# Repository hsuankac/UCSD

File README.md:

# UCSD
Embedded Systems Engineering Certificate

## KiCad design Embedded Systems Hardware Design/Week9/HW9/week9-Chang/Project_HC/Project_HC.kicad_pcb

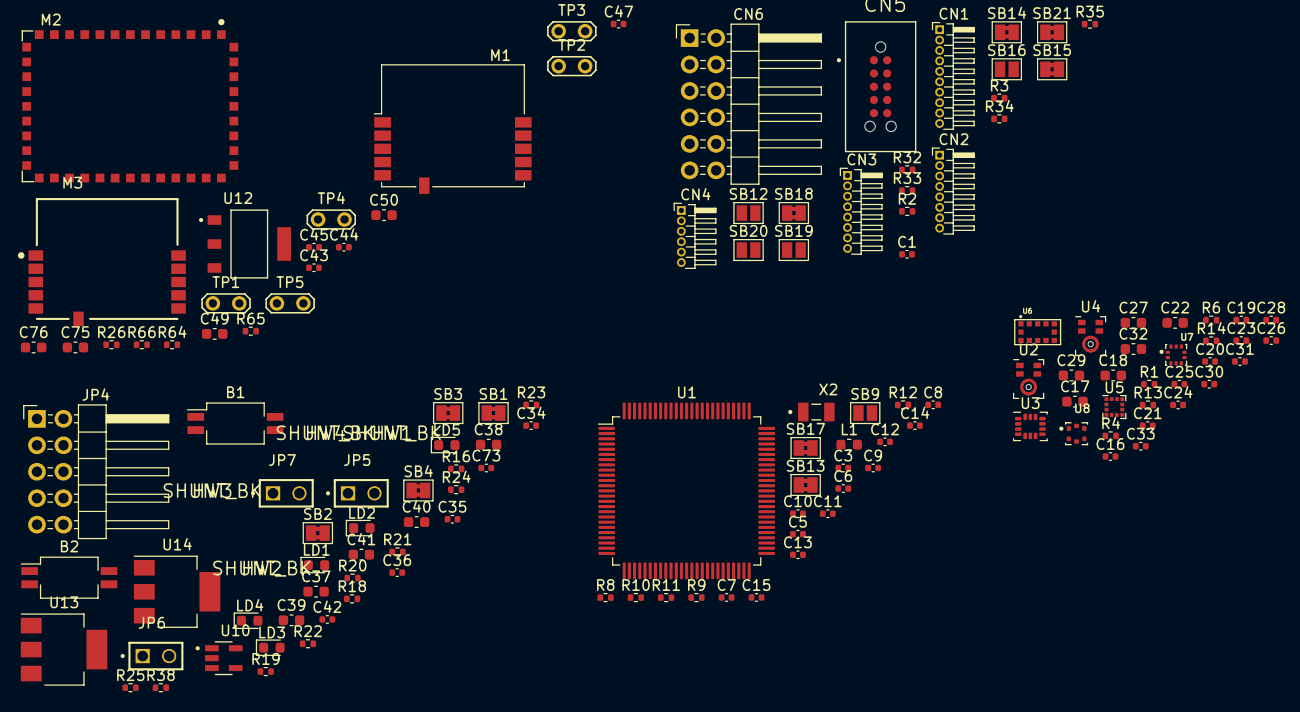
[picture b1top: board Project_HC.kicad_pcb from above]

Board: 2 copper layers, 137 parts (0 on the bottom side), 91 nets, no tracks yet.

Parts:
B1: SW-PUSH-CMS_BLUE; SW_DIP_SPSTx02_Slide_Copal_CHS-02B_W7.62mm_P1.27mm
B2: SW-PUSH-CMS_BLACK; SW_DIP_SPSTx02_Slide_Copal_CHS-02B_W7.62mm_P1.27mm
C1, C3, C5, C6, C7, C9, C10, C11, C12, C13, C16, C19, C20, C21, C23, C25, C26, C28, C30, C31, C33, C34, C36, C42, C43, C44, C45, C73: 100nF; C_0402_1005Metric
C8, C24: 1uF; C_0402_1005Metric
C14, C15: 5.1pF; C_0402_1005Metric
C17, C22: 10uf; C_0603_1608Metric
C18, C27, C32: 4.7uF; C_0603_1608Metric
C29, C75, C76: 2.2uF; C_0603_1608Metric
C35: 10pF; C_0402_1005Metric
C37: 10pF; C_0603_1608Metric
C38, C39, C40, C41, C49, C50: 10uF; C_0603_1608Metric
C47: 2.2uF; C_0402_1005Metric
CN1: Header 10X1_Female_SMD; PinHeader_1x10_P1.00mm_Horizontal
CN2, CN3: Header 8X1_Female_SMD; PinHeader_1x08_P1.00mm_Horizontal
CN4: Header 6X1_Female_SMD; PinHeader_1x06_P1.00mm_Horizontal
CN5: TC2050-IDC-NL; TAG-CONNECT_TC2050-IDC-NL
CN6: HEADER_2X6_PMOD; PinHeader_2x06_P2.54mm_Horizontal
HW1, HW2, HW3, HW4: SHUNT_BK; Samtec-SNT-100-BK-G-MFG
JP4: HEADER_2X5; PinHeader_2x05_P2.54mm_Horizontal
JP5, JP6, JP7: TSW-102-07-G-S; SAMTEC_TSW-102-07-G-S
L1: FCM1608KF-601T03; L_0603_1608Metric
LD1, LD2, LD3: LED GREEN; LED_0603_1608Metric
LD4: LED YELLOW; LED_0603_1608Metric
LD5: LED BLUE; LED_0603_1608Metric
M1: BT Module; ST_SPBTLE
M2: ISM43362-M3G-L44; INVENTEK_ISM43362-M3G-L44-E_C2.5.0.3_SPI
M3: SPSGRF; XCVR_SPSGRF-868
R1, R2, R4, R12: 0R; R_0402_1005Metric
R3: 1k; R_0402_1005Metric
R6, R13: 10k; R_0402_1005Metric
R8, R11: 2K2; R_0402_1005Metric
R9, R10: 2k2; R_0402_1005Metric
R14, R16: 10K; R_0402_1005Metric
R18, R19, R21, R24: 1K; R_0402_1005Metric
R20, R25: 330R; R_0402_1005Metric
R22: 680R; R_0402_1005Metric
R23: 100k; R_0402_1005Metric
R26: 47K; R_0402_1005Metric
R32, R33, R34, R35: 22R; R_0402_1005Metric
R38: 200k; R_0402_1005Metric
R64, R65, R66: Not Fitted (10k); R_0402_1005Metric
SB1, SB2, SB3, SB4, SB13, SB14, SB15, SB17, SB18, SB21: Close; SolderJumper-2_P1.3mm_Bridged2Bar_Pad1.0x1.5mm
SB9, SB12, SB16, SB19, SB20: Open; SolderJumper-2_P1.3mm_Open_Pad1.0x1.5mm
TP1, TP2, TP3, TP4, TP5: TestPoint_Small; TestPoint_2Pads_Pitch2.54mm_Drill0.8mm
U1: STM32L475VGTx; LQFP-100_14x14mm_P0.5mm
U2, U4: Mic; Knowles_LGA-5_3.5x2.65mm
U3: LSM6DSL; LGA-14_3x2.5mm_P0.5mm_LayoutBorder3x4y
U5: LIS3MDL; LGA-12_2x2mm_P0.5mm
U6: VL53L0X; SENSOR_VL53L0X
U7: LPS22HB; LGA10R50P2X3_200X200X80
U8: HTS221; XDCR_HTS221
U10: TSV631AILT; SOT95P280X145-5N
U12: LT1963EST-3.3; SOT230P700X180-4N
U13: LD1117S50TR; SOT-223-3_TabPin2
U14: LD1117S33TR; SOT-223-3_TabPin2
X2: NX3215SA-32.768K; XTAL_NX3215SA-32.768K-STD-MUA-8

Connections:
+3.3V: C16.1, C17.1, C21.1, C22.1, C27.1, C28.1, C29.1, C30.1, C73.1, R6.2, R23.2, U2.1 (Vdd), U4.1 (Vdd), U6.1 (AVDDVCSEL), U6.11 (AVDD), U8.1 (VDD), U8.6 (CS), U10.5 (V+)
+3V3: C18.1, C19.1, C20.1, C24.1, C25.1, C26.1, C31.1, C32.1, C33.1, C42.1, C43.1, C44.1, C45.1, C47.1, C50.1, C75.1, C76.1, CN2.2 (IOREF), CN2.4 (3V3), CN6.6, CN6.12, JP5.01, JP5.02, M1.5 (VIN), M2.2 (VDD), M2.14 (VDD), M2.15 (VBAT), M3.5 (VIN), R8.1, R9.1, R10.1, R11.1, R13.2, R14.2, R26.2, R64.2, R65.2, R66.2, U3.5 (VDDIO), U3.8 (VDD), U3.12 (CS), U5.5 (Vdd), U5.6 (Vdd_IO), U5.9 (SDO/SA1), U5.10 (~CS), U7.1 (VDD_IO), U7.5 (SD0/SA0), U7.6 (~CS), U7.10 (VDD), U12.3 (OUT)
+5V: C1.1, C38.1, C39.1, C40.1, C41.1, C49.1, CN2.5, CN2.8 (VIN), CN5.1, JP4.1, JP4.2, JP4.3, JP4.4, JP4.5, JP4.6, JP4.8, JP4.9, JP4.10, R2.1, R3.2, R25.2, U12.1 (IN), U13.2 (VO), U13.3 (VI), U14.2 (VO), U14.3 (VI)
ARD.A0-ADC: CN4.1, U1.34 (PC5)
ARD.A1-ADC: CN4.2, U1.33 (PC4)
ARD.A2-ADC: CN4.3, U1.18 (PC3)
ARD.A3-ADC: CN4.4, U1.17 (PC2)
ARD.A4-ADC: CN4.5, U1.16 (PC1)
ARD.A5-ADC: CN4.6, U1.15 (PC0)
ARD.D0-UART4_RX: CN3.1, U1.24 (PA1)
ARD.D1-UART4_TX: CN3.2, U1.23 (PA0)
ARD.D2-INT0_EXTI14: CN3.3, U1.61 (PD14)
ARD.D3-PWM/INT1_EXTI0: CN3.4, U1.35 (PB0)
ARD.D4: CN3.5, U1.26 (PA3)
ARD.D5-PWM: CN3.6, U1.90 (PB4)
ARD.D6-PWM: CN3.7, U1.36 (PB1)
ARD.D7: CN3.8, U1.29 (PA4)
ARD.D8: CN1.1, U1.37 (PB2)
ARD.D9-PWM: CN1.2, U1.77 (PA15)
ARD.D10-SPI_SSN/PWM: CN1.3, U1.25 (PA2)
ARD.D11-SPI1_MOSI/PWM: CN1.4, U1.32 (PA7)
ARD.D12-SPI1_MISO: CN1.5, U1.31 (PA6)
ARD.D13-SPI1_SCK/LED1: CN1.6, U1.30 (PA5)
ARD.D14-I2C1_SDA: CN1.9, R8.2, U1.96 (PB9)
ARD.D15-I2C1_SCL: CN1.10, R9.2, U1.95 (PB8)
DFSDM1_CKOUT: R1.1, U1.40 (PE9), U1.41 (PE10)
DFSDM1_DATIN2: R4.1, U1.38 (PE7)
GND: B1.2, B2.2, C1.2, C3.2, C5.2, C6.2, C7.2, C8.2, C9.1, C10.1, C11.1, C12.1, C13.1, C14.2, C15.2, C16.2, C17.2, C18.2, C19.2, C20.2, C21.2, C22.2, C23.2, C24.2, C25.2, C26.2, C27.2, C28.2, C29.2, C30.2, C31.2, C32.2, C33.2, C34.2, C35.2, C36.2, C37.2, C38.2, C39.2, C40.2, C41.2, C42.2, C43.2, C44.2, C45.2, C47.2, C49.2, C50.2, C73.2, C75.2, C76.2, CN1.7, CN2.6, CN2.7 (GND), CN5.3, CN5.5, CN6.5, CN6.11, JP6.01, JP6.02, JP7.01, JP7.02, LD1.1 (K), LD2.1 (K), LD3.1 (K), LD4.1 (K), LD5.1 (K), M1.6 (GND), M2.1 (GND), M2.3 (GND), M2.17 (GND), M2.20 (GND), M2.35 (GND), M3.6 (GND), R38.2, SB13.1 (A), U1.10 (VSS), U1.19 (VSSA), U1.20 (VREF-), U1.27 (VSS), U1.49 (VSS), U1.74 (VSS), U1.99 (VSS), U2.5 (GND), U3.1 (SDO/SA0), U3.6 (GND), U3.7 (GND), U4.2 (LR), U4.5 (GND), U5.2 (Res), U5.3 (GND), U5.12 (Res), U6.2 (AVSSVCSEL), U6.3 (GND), U6.4 (GND), U6.6 (GND), U6.12 (GND), U7.3 (RES), U7.8 (GND), U7.9 (GND), U8.5 (GND), U10.2 (V-), U12.2 (GND), U13.1 (GND), U14.1 (GND)
HTS221_DRDY_EXTI15: U1.62 (PD15), U8.3 (DRDY)
INTERNAL-I2C2_SCL: R10.2, U1.47 (PB10), U3.13 (SCL), U5.1 (SCL/SPC), U6.10 (SCL), U7.2 (SCL/SPC), U8.2 (SCL/SPC)
INTERNAL-I2C2_SDA: U3.4 (INT1), U3.14 (SDA), U5.11 (SDA/SDI/SDO), U6.9 (SDA), U7.4 (SDA/SDI/SDO), U8.4 (SDA/SDI/SDO)
INTERNAL-SPI3_MISO: M1.8 (SPI_MISO), M2.10 (ADC3/SPI_MISO), M3.8 (SPI_MISO), U1.79 (PC11)
INTERNAL-SPI3_MOSI: M1.9 (SPI_MOSI), M2.9 (ADC4/SPI_MOSI), M3.9 (SPI_MOSI), U1.80 (PC12)
INTERNAL-SPI3_SCK: M1.7 (SPI_CLK), M2.11 (ADC2/SPI_SCK), M3.7 (SPI_CLK), U1.78 (PC10)
INTERNAL-UART3_RX: M2.22 (TX), U1.56 (PD9)
INTERNAL-UART3_TX: M2.21 (RX), U1.55 (PD8)
ISM43362-BOOT0: M2.33 (BOOT0/RES4), U1.51 (PB12)
ISM43362-DRDY_EXTI1: M2.13 (ADC0/DATARDY), U1.98 (PE1)
ISM43362-RST: M2.34 (RSTN), U1.39 (PE8)
ISM43362-WAKEUP: M2.16 (WKUP), U1.52 (PB13)
LED2: R20.2, U1.53 (PB14)
LED3(WIFI) & LED4(BLE): R21.2, R22.2, U1.66 (PC9)
LPS22HB_INT_DRDY_EXTI10: U1.57 (PD10), U7.7 (INT_DRDY)
LSM3MDL_DRDY_EXTI8: U1.65 (PC8), U5.8 (DRDY)
NTERNAL-I2C2_SDA: R11.2, U1.48 (PB11)
unnamed: B1.1, C37.1, R23.1, R24.1
unnamed: B2.1, C35.1, R19.1
unnamed: C5.1, C6.1, L1.2, U1.21 (VREF+), U1.22 (VDDA)
unnamed: C14.1, R12.2, X2.1
unnamed: C15.1, U1.9 (PC15), X2.2
unnamed: C23.1, U5.4 (C1)
unnamed: C34.1, R19.2
unnamed: C36.1, R24.2
unnamed: CN1.8, R2.2
unnamed: CN2.1, R3.1
unnamed: CN5.2, R33.1
unnamed: CN5.4, R32.1
unnamed: CN5.6, R35.1
unnamed: CN5.10, R34.1
unnamed: LD1.2 (A), R25.1
unnamed: LD2.2 (A), R18.1
unnamed: LD3.2 (A), R20.1
unnamed: LD4.2 (A), R21.1
unnamed: LD5.2 (A), R22.1
unnamed: M2.4 (TMS), TP1.1
unnamed: M2.5 (TCK), TP2.1
unnamed: M2.6 (TDI), TP3.1
unnamed: M2.7 (TDO), TP4.1
unnamed: M2.8 (TDRSTN), TP5.1
unnamed: M2.28 (CFG0), R66.1
unnamed: M2.29 (CFG1), R64.1, R65.1
unnamed: R1.2, U2.3 (CLK), U4.3 (CLK)
unnamed: R4.2, U2.4 (Dout), U4.4 (Dout)
unnamed: R6.1, U2.2 (LR)
unnamed: R12.1, U1.8 (PC14)
unnamed: R16.1, R38.1, U10.1 (+)
unnamed: R18.2, U10.3 (-), U10.4
unnamed: SB9.2 (B), SB13.2 (B), U1.94 (BOOT0)
PMOD-IRQ_EXTI2: CN6.7, U1.83 (PD2)
PMOD-RESET: CN6.8, U1.81 (PD0)
SPBTLE-RF-IRQ_EXTI6: M1.4 (SPI_IRQ), U1.5 (PE6)
SPBTLE-RF-RST: M1.11 (~BT_RESET), U1.67 (PA8)
SPBTLE-RF-SPI3-CSN: M1.10 (SPI_~CS), M2.12 (ADC1/SPI_SSN), M3.10 (SPI_CS), R26.1
SPSGRF-915-GPIO3_EXTI5: M3.1 (GPIO[3]), U1.4 (PE5)
SPSGRF-915-SDN: M3.11 (SDN), U1.54 (PB15)
STM_NRST: C3.1, CN2.3 (NRST), R33.2, R34.2, U1.14 (NRST)
SYS_JTCK-SWCLK: R32.2, U1.76 (PA14)
SYS_JTDO-SWO: R35.2, U1.89 (PB3)
VDD: C7.1, C8.1, C9.2, C10.2, C11.2, C12.2, C13.2, L1.1, SB9.1 (A), SB17.1 (A), SB17.2 (B), U1.6 (VBAT), U1.11 (VDD), U1.28 (VDD), U1.50 (VDD), U1.73 (VDDUSB), U1.75 (VDD), U1.100 (VDD)
VL53L0X_GPIO1_EXTI7: R13.1, U1.64 (PC7), U6.7 (GPIO1)
VL53L0X_XSHUT: R14.1, U1.63 (PC6), U6.5 (~XSHUT)

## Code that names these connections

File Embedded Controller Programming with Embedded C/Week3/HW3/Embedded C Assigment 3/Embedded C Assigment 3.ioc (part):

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Mcu.Name=STM32L475V(C-E-G)Tx
Mcu.Package=LQFP100
Mcu.UserName=STM32L475VGTx
PA0.GPIOParameters=GPIO_Label
PA0.GPIO_Label=ARD_D1 [UART4_TX]
PA0.Signal=UART4_TX
PA1.GPIOParameters=GPIO_Label
PA1.GPIO_Label=ARD_D0 [UART4_RX]
PA1.Signal=UART4_RX
PA10.GPIOParameters=GPIO_Label
PA10.GPIO_Label=USB_OTG_FS_ID
PA10.Signal=USB_OTG_FS_ID
PA11.GPIOParameters=GPIO_Label
PA11.GPIO_Label=USB_OTG_FS_DM
PA11.Mode=Device_Only
PA11.Signal=USB_OTG_FS_DM
PA12.GPIOParameters=GPIO_Label
PA12.GPIO_Label=USB_OTG_FS_DP
PA12.Mode=Device_Only
PA12.Signal=USB_OTG_FS_DP
PA13\ (JTMS-SWDIO).GPIOParameters=GPIO_Label
PA13\ (JTMS-SWDIO).GPIO_Label=SYS_JTMS_SWDIO
PA13\ (JTMS-SWDIO).Mode=Serial_Wire
PA13\ (JTMS-SWDIO).Signal=SYS_JTMS-SWDIO
PA14\ (JTCK-SWCLK).GPIOParameters=GPIO_Label
PA14\ (JTCK-SWCLK).GPIO_Label=SYS_JTCK_SWCLK
PA14\ (JTCK-SWCLK).Mode=Serial_Wire
PA14\ (JTCK-SWCLK).Signal=SYS_JTCK-SWCLK
PA15\ (JTDI).GPIOParameters=GPIO_Label
PA15\ (JTDI).GPIO_Label=ARD_D9
PA15\ (JTDI).Signal=GPIO_Output
PA2.GPIOParameters=GPIO_Label
PA2.GPIO_Label=ARD_D10 [SPI_SSN]
PA2.Signal=GPIO_Output
PA3.GPIOParameters=GPIO_Label
PA3.GPIO_Label=ARD_D4
PA3.Signal=S_TIM2_CH4
PA4.GPIOParameters=GPIO_Label
PA4.GPIO_Label=ARD_D7
PA4.Signal=ADCx_IN9
PA5.GPIOParameters=GPIO_Label
PA5.GPIO_Label=ARD_D13 [SPI1_SCK]
PA5.Signal=SPI1_SCK
PA6.GPIOParameters=GPIO_Label
PA6.GPIO_Label=ARD_D12 [SPI1_MISO]
PA6.Signal=SPI1_MISO
PA7.GPIOParameters=GPIO_Label
PA7.GPIO_Label=ARD_D11 [SPI1_MOSI]
PA7.Signal=SPI1_MOSI
PA8.GPIOParameters=GPIO_Label
PA8.GPIO_Label=SPBTLE_RF_RST
PA8.Signal=GPIO_Output
PA9.GPIOParameters=GPIO_Label
PA9.GPIO_Label=USB_OTG_FS_VBUS [STMPS2141STR_OUT]
PA9.Signal=USB_OTG_FS_VBUS
PB0.GPIOParameters=GPIO_Label
PB0.GPIO_Label=ARD_D3 [INT_EXT10]
PB0.Signal=GPXTI0
PB1.GPIOParameters=GPIO_Label
PB1.GPIO_Label=ARD_D6 [ADC1_IN6]
PB1.Signal=ADCx_IN16
PB10.GPIOParameters=GPIO_Label,GPIO_Pu
PB10.GPIO_Label=INTERNAL_I2C2_SCL [VL53L0X_SCL]
PB10.GPIO_Pu=GPIO_PULLUP
PB10.Mode=I2C
PB10.Signal=I2C2_SCL
PB11.GPIOParameters=GPIO_Label,GPIO_Pu
PB11.GPIO_Label=INTERNAL_I2C2_SDA [VL53L0X_SDA]
PB11.GPIO_Pu=GPIO_PULLUP
PB11.Mode=I2C
PB11.Signal=I2C2_SDA
PB12.GPIOParameters=GPIO_Label
PB12.GPIO_Label=ISM43362_BOOT0 [ISM43362_BOOT]
PB12.Signal=GPIO_Output
PB13.GPIOParameters=GPIO_Label
PB13.GPIO_Label=ISM43362_WAKEUP [ISM43362_WKUP]
PB13.Signal=GPIO_Output
PB14.GPIOParameters=GPIO_Label
PB14.GPIO_Label=LED2 [LED_GREEN]
PB14.Signal=GPIO_Output
PB15.GPIOParameters=GPIO_Label
PB15.GPIO_Label=SPSGRF_915_SDN [SPSGRF_SDN]
PB15.Signal=GPIO_Output
PB2.GPIOParameters=GPIO_Label
PB2.GPIO_Label=ARD_D8
PB2.Signal=GPIO_Output
PB3\ (JTDO-TRACESWO).GPIOParameters=GPIO_Label
PB3\ (JTDO-TRACESWO).GPIO_Label=SYS_JTD0_SWO
PB3\ (JTDO-TRACESWO).Signal=SYS_JTDO-SWO
PB4\ (NJTRST).GPIOParameters=GPIO_Label
PB4\ (NJTRST).GPIO_Label=ARD_D5
PB4\ (NJTRST).Signal=GPIO_Output
PB5.GPIOParameters=PinState,GPIO_Label
PB5.GPIO_Label=SPSGRF_915_SPI3_CSN [SPSGRF_SPI_CS]
PB5.PinState=GPIO_PIN_SET
PB5.Signal=GPIO_Output
PB6.GPIOParameters=GPIO_Label
PB6.GPIO_Label=ST_LINK_UART1_TX
PB6.Mode=Asynchronous
PB6.Signal=USART1_TX
PB7.GPIOParameters=GPIO_Label
PB7.GPIO_Label=ST_LINK_UART1_RX
PB7.Mode=Asynchronous
PB7.Signal=USART1_RX
PB8.GPIOParameters=GPIO_Label
PB8.GPIO_Label=ARD_D15 [I2C1_SCL]
PB8.Signal=I2C1_SCL
PB9.GPIOParameters=GPIO_Label
PB9.GPIO_Label=ARD_D14 [I2C1_SDA]
PB9.Signal=I2C1_SDA
PC0.GPIOParameters=GPIO_Label
PC0.GPIO_Label=ARD_A5 [ADC]
PC0.Signal=ADCx_IN1
PC1.GPIOParameters=GPIO_Label
PC1.GPIO_Label=ARD_A4 [ADC]
PC1.Signal=ADCx_IN2
PC10.GPIOParameters=GPIO_Label
PC10.GPIO_Label=INTERNAL_SPI3_SCK [BT module_SPI_SCLK] [ISM43362_SCK]
PC10.Mode=Full_Duplex_Master
PC10.Signal=SPI3_SCK
PC11.GPIOParameters=GPIO_Label
PC11.GPIO_Label=INTERNAL_SPI3_MISO [BT module_SPI_MISO] [ISM43362_MISO]
PC11.Mode=Full_Duplex_Master
PC11.Signal=SPI3_MISO
PC12.GPIOParameters=GPIO_Label
PC12.GPIO_Label=INTERNAL_SPI3_MOSI [BT module_SPI_MOSI] [ISM43362_MOSI]
PC12.Mode=Full_Duplex_Master
PC12.Signal=SPI3_MOSI
PC13.Signal=GPIO_Input
PC14-OSC32_IN\ (PC14).Mode=LSE-External-Oscillator
PC14-OSC32_IN\ (PC14).Signal=RCC_OSC32_IN
PC15-OSC32_OUT\ (PC15).Mode=LSE-External-Oscillator
PC15-OSC32_OUT\ (PC15).Signal=RCC_OSC32_OUT
PC2.GPIOParameters=GPIO_Label
PC2.GPIO_Label=ARD_A3 [ADC]
PC2.Signal=ADCx_IN3
PC3.GPIOParameters=GPIO_Label
PC3.GPIO_Label=ARD_A2 [ADC]
PC3.Signal=ADCx_IN4
PC4.GPIOParameters=GPIO_Label
PC4.GPIO_Label=ARD_A1 [ADC]
PC4.Signal=ADCx_IN13
PC5.GPIOParameters=GPIO_Label
PC5.GPIO_Label=ARD_A0 [ADC]
PC5.Signal=ADCx_IN14
PC6.GPIOParameters=GPIO_Label
PC6.GPIO_Label=VL53L0X_XSHUT [Read_XSHUT]
PC6.Signal=GPIO_Output
PC7.GPIOParameters=GPIO_Label
PC7.GPIO_Label=VL53L0X_GPIO1_EXTI7 [VL53L0X_GPIO1]
PC7.Signal=GPXTI7
PC8.GPIOParameters=GPIO_Label
PC8.GPIO_Label=LSM3MDL_DRDY_EXTI8 [LIS3MDL_DRDY]
PC8.Signal=GPXTI8
PC9.GPIOParameters=GPIO_Label
PC9.GPIO_Label=LED3_WIFI_ LED4_BLE
PC9.Signal=GPIO_Output
PD0.GPIOParameters=GPIO_Label
PD0.GPIO_Label=PMOD_RESET
PD0.Signal=GPIO_Output
PD1.GPIOParameters=GPIO_Label
PD1.GPIO_Label=PMOD_SPI2_SCK
PD1.Signal=SPI2_SCK
PD10.GPIOParameters=GPIO_Label
PD10.GPIO_Label=LPS22HB_INT_DRDY_EXTI0 [LPS22HB_INT_DRDY] 
PD10.Signal=GPXTI10
PD11.GPIOParameters=GPIO_Label
PD11.GPIO_Label=LSM6DSL_INT1_EXTI11 [LSM6DSL_INT1]
PD11.Signal=GPXTI11
PD12.GPIOParameters=GPIO_Label
PD12.GPIO_Label=USB_OTG_FS_PWR_EN [STMPS2141STR_EN]
PD12.Signal=GPIO_Output
PD13.GPIOParameters=PinState,GPIO_Label
PD13.GPIO_Label=SPBTLE_RF_SPI3_CSN [BT module_SPI_CS]
PD13.PinState=GPIO_PIN_SET
PD13.Signal=GPIO_Output
PD14.GPIOParameters=GPIO_Label
PD14.GPIO_Label=ARD_D2 [INT0_EXTI14]
PD14.Signal=GPXTI14
PD15.GPIOParameters=GPIO_Label
PD15.GPIO_Label=HTS221_DRDY_EXTI15 [HTS221_DRDY]
PD15.Signal=GPXTI15
PD2.GPIOParameters=GPIO_Label
PD2.GPIO_Label=PMOD_IRQ_EXTI12
PD2.Signal=GPXTI2
PD3.GPIOParameters=GPIO_Label
PD3.GPIO_Label=PMOD_UART2_CTS
PD3.Signal=USART2_CTS
PD4.GPIOParameters=GPIO_Label
PD4.GPIO_Label=PMOD_UART2_RTS
PD4.Signal=USART2_RTS
PD5.GPIOParameters=GPIO_Label
PD5.GPIO_Label=PMOD_UART2_TX
PD5.Signal=USART2_TX
PD6.GPIOParameters=GPIO_Label
PD6.GPIO_Label=PMOD_UART2_RX
PD6.Signal=USART2_RX
PD7.GPIOParameters=GPIO_Label
PD7.GPIO_Label=STSAFE_A100_RESET [STSAFE-A100_RESET]
PD7.Signal=GPIO_Output
PD8.GPIOParameters=GPIO_Label
PD8.GPIO_Label=INTERNAL_UART3_TX [ISM43362_RX]
PD8.Mode=Asynchronous
PD8.Signal=USART3_TX
PD9.GPIOParameters=GPIO_Label
PD9.GPIO_Label=INTERNAL_UART3_RX [ISM43362_TX]
PD9.Mode=Asynchronous
PD9.Signal=USART3_RX
PE0.GPIOParameters=PinState,GPIO_Label
PE0.GPIO_Label=ISM43362_SPI3_CSN [ISM43362_SSN]
PE0.PinState=GPIO_PIN_SET
PE0.Signal=GPIO_Output
PE1.GPIOParameters=GPIO_Label
PE1.GPIO_Label=ISM43362_DRDY_EXTI1 [ISM43362_DATARDY]
PE1.Signal=GPXTI1
PE10.GPIOParameters=GPIO_Label
PE10.GPIO_Label=QUADSPI_CLK [MX25R6435F_SCLK]
PE10.Mode=Single Bank
PE10.Signal=QUADSPI_CLK
PE11.GPIOParameters=GPIO_Label
PE11.GPIO_Label=QUADSPI_NCS [MX25R6435F_SCLK]
PE11.Mode=Single Bank
PE11.Signal=QUADSPI_NCS
PE12.GPIOParameters=GPIO_Label
PE12.GPIO_Label=OQUADSPI_BK1_IO0 [MX25R6435F_IO0]
PE12.Mode=Single Bank
PE12.Signal=QUADSPI_BK1_IO0
PE13.GPIOParameters=GPIO_Label
PE13.GPIO_Label=QUADSPI_BK1_IO1 [MX25R6435F_IO1]
PE13.Mode=Single Bank
PE13.Signal=QUADSPI_BK1_IO1
PE14.GPIOParameters=GPIO_Label
PE14.GPIO_Label=QUAD_SPI_BK1_IO2 [MX25R6435F_IO2]
PE14.Mode=Single Bank
PE14.Signal=QUADSPI_BK1_IO2
PE15.GPIOParameters=GPIO_Label
PE15.GPIO_Label=QUAD_SPI_BK1_IO3 [MX25R6435F_IO3]
PE15.Mode=Single Bank
PE15.Signal=QUADSPI_BK1_IO3
PE2.GPIOParameters=GPIO_Label
PE2.GPIO_Label=M24SR64_Y_RF_DISABLE [M24SR64_RFDIS]
PE2.Signal=GPIO_Output
PE3.GPIOParameters=GPIO_Label
PE3.GPIO_Label=USB_OTG_FS_OVRCR_EXTI3 [STMPS2141STR_FAULT]
PE3.Signal=GPXTI3
PE4.GPIOParameters=GPIO_Label
PE4.GPIO_Label=M24SR64_Y_GPO [M24SR64_GPO]
PE4.Signal=GPIO_Output
PE5.GPIOParameters=GPIO_Label
PE5.GPIO_Label=SPSGRF_915_GPIO3_EXTI5 [SPSGRF_GPIO_3]
PE5.Signal=GPXTI5
PE6.GPIOParameters=GPIO_Label
PE6.GPIO_Label=SPBTLE_RF_IRQ_EXTI6 [BT module_SPI_IRQ]
PE6.Signal=GPXTI6
PE7.GPIOParameters=GPIO_Label
PE7.GPIO_Label=DFSDM1_DATIN2 [MP34DT01_DOUT]
PE7.Signal=S_DATAIN2DFSDM1
PE8.GPIOParameters=GPIO_Label
PE8.GPIO_Label=ISM43362_RST [ISM43362_RSTN]
PE8.Signal=GPIO_Output
PE9.GPIOParameters=GPIO_Label
PE9.GPIO_Label=DFSDM1_CKOUT [MP34DT01_CLK]
PE9.Signal=S_CKOUTDFSDM1
RCC.HSE_VALUE=8000000
RCC.SYSCLKFreq_VALUE=80000000
RCC.SYSCLKSource=RCC_SYSCLKSOURCE_PLLCLK
board=B-L475E-IOT01A2
boardIOC=true

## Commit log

2023-02-09 Add ESHD course
2023-02-17 HW5 finished
2023-02-17 HW6 finished
2023-03-10 Final report finished
2023-03-13 Add final answer and file clean-up
2023-03-30 Week 1
2023-03-30 Week 1 finished
2023-04-06 Finish week 2
2023-04-14 Finish week 3
2023-04-24 Finish week 4
2023-04-30 Finish week 5
2023-05-12 Finish week 7
2023-05-20 Finish week8
2023-05-26 Finish course Embedded Controller Programming with Embedded C
2023-08-09 Add embedded hardware interfacing course and embedded controller programming for real-time systems
2023-08-15 Embedded system hardware interfacing week 6
2023-08-17 Embedded Controller Programming for Real-Time Systems midterm finished
2023-08-24 Finish Embedded system hardware interfacing week 7 and real-time system week 6
2023-08-29 Embedded system hardware interfacing week8 finished
2023-08-30 Embedded system hardware interfacing week9 finished
2023-09-07 Finish Embedded Controller Programming for Real-Time Systems and Embedded Systems Hardware Interfacing courses
2023-10-10 Finish embedded RTOS and embedded Linux week 3
2023-10-18 Finish Embedded RTOS week 4
2023-10-19 Finish embedded linux week 4
2023-10-24 Finished Embedded RTOS week5
2023-10-25 Finish embedded linux week 5
2023-11-07 Finish embedded linux week 6
2023-11-14 Finished embedded linux week 7
2023-11-18 Finished embedded linux week 8
2023-11-19 Finised embedded linux course
2023-11-22 Finished embedded RTOS final project
